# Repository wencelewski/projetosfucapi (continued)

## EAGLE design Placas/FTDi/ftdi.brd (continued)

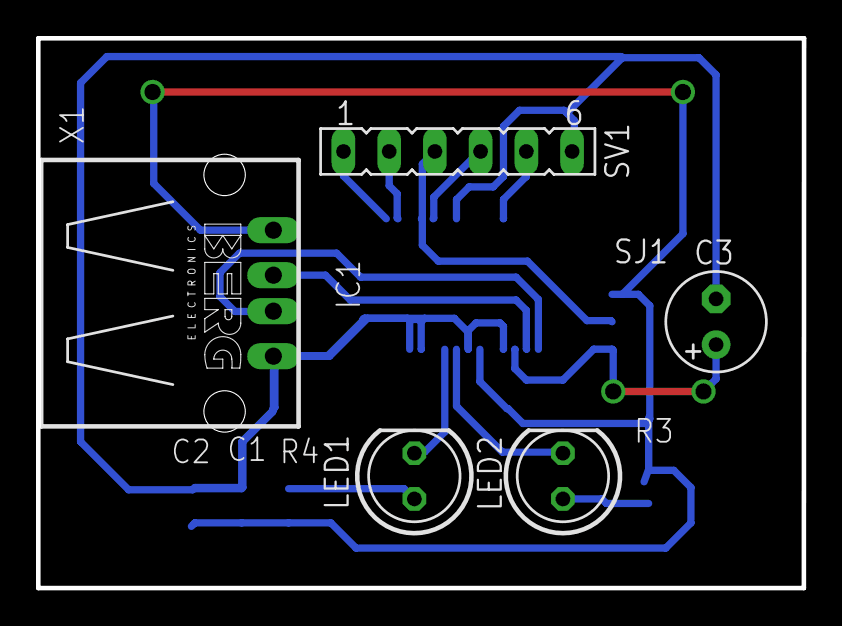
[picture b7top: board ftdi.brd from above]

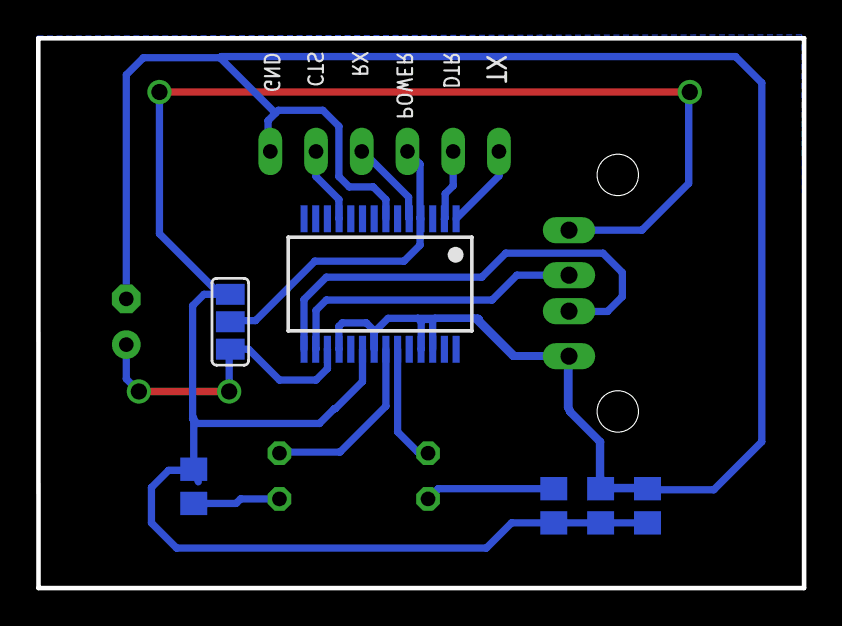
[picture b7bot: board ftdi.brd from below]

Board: 2 copper layers, 42.5 x 30.5 mm, 11 parts (6 on the bottom side), 14 nets.

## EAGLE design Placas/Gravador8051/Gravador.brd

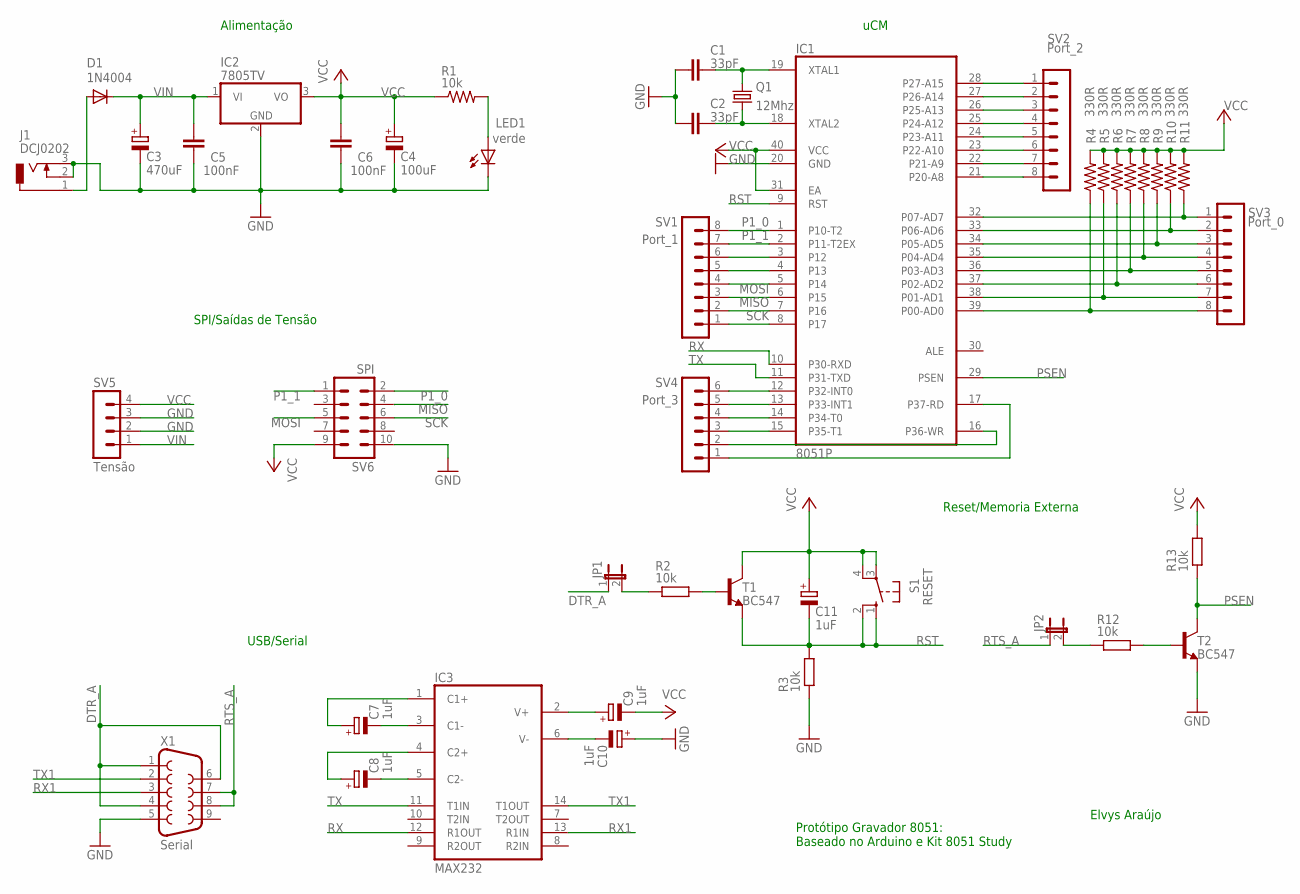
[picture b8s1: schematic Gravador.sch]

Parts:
C1, C2: 33pF; C5B3
C3: 470uF; E3,5-8
C4: 100uF; E2,5-6E
C5, C6: 100nF; C5B3
C7, C8, C9, C10, C11: 1uF; E2,5-6E
D1: 1N4004; DO41-10
IC1: 8051P; DIL40
IC2: 7805TV; TO220V
IC3: MAX232; DIL16
J1: DCJ0202
JP1, JP2: JP1E; JP1
LED1: verde; LED5MM
Q1: 12Mhz; HC49U-V
R1: 10k; 0207/2V
R2, R3, R12, R13: 10k; 0207/10@1
R4, R5, R6, R7, R8, R9, R10, R11: 330R; 0207/2V
S1: RESET; B3F-10XX
SV1: Port_1; MA08-1
SV2: Port_2; MA08-1
SV3: Port_0; MA08-1
SV4: Port_3; MA06-1
SV5: Tensão; MA04-1
SV6: SPI; MA05-2
T1, T2: BC547; TO92
X1: Serial; F09HP

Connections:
DTR_A: JP1.1, X1.1, X1.4, X1.6
GND: C1.2, C2.2, C3.-, C4.-, C5.2, C6.2, C10.+, IC1.20 (GND), IC2.2 (GND), IC3.15 (GND), J1.2, J1.3, LED1.K (C), R3.1, SV5.2, SV5.3, SV6.10, T2.1 (E), X1.5
MISO: IC1.7 (P16), SV1.2, SV6.4
MOSI: IC1.6 (P15), SV1.3, SV6.5
unnamed: C1.1, IC1.19 (XTAL1), Q1.1
unnamed: C2.1, IC1.18 (XTAL2), Q1.2
unnamed: IC1.15 (P35-T1), SV4.3
unnamed: IC1.14 (P34-T0), SV4.4
unnamed: IC1.5 (P14), SV1.4
unnamed: IC1.4 (P13), SV1.5
unnamed: IC1.3 (P12), SV1.6
unnamed: IC1.28 (P27-A15), SV2.1
unnamed: IC1.27 (P26-A14), SV2.2
unnamed: IC1.26 (P25-A13), SV2.3
unnamed: IC1.25 (P24-A12), SV2.4
unnamed: IC1.24 (P23-A11), SV2.5
unnamed: IC1.23 (P22-A10), SV2.6
unnamed: IC1.22 (P21-A9), SV2.7
unnamed: IC1.21 (P20-A8), SV2.8
unnamed: IC1.13 (P33-INT1), SV4.5
unnamed: IC1.32 (P07-AD7), R11.1, SV3.1
unnamed: IC1.33 (P06-AD6), R10.1, SV3.2
unnamed: IC1.34 (P05-AD5), R9.1, SV3.3
unnamed: IC1.35 (P04-AD4), R8.1, SV3.4
unnamed: IC1.36 (P03-AD3), R7.1, SV3.5
unnamed: IC1.37 (P02-AD2), R6.1, SV3.6
unnamed: IC1.38 (P01-AD1), R5.1, SV3.7
unnamed: IC1.12 (P32-INT0), SV4.6
unnamed: IC1.16 (P36-WR), SV4.2
unnamed: IC1.17 (P37-RD), SV4.1
unnamed: LED1.A, R1.2
unnamed: C7.+, IC3.1 (C1+)
unnamed: D1.A, J1.1
unnamed: C7.-, IC3.3 (C1-)
unnamed: C8.+, IC3.4 (C2+)
unnamed: C8.-, IC3.5 (C2-)
unnamed: C9.+, IC3.2 (V+)
unnamed: C10.-, IC3.6 (V-)
unnamed: JP1.2, R2.1
unnamed: R2.2, T1.2 (B)
unnamed: IC1.39 (P00-AD0), R4.1, SV3.8
unnamed: JP2.2, R12.1
unnamed: R12.2, T2.2 (B)
P1_0: IC1.1 (P10-T2), SV1.8, SV6.2
P1_1: IC1.2 (P11-T2EX), SV1.7, SV6.1
PSEN: IC1.29 (PSEN), R13.1, T2.3 (C)
RST: C11.-, IC1.9 (RST), R3.2, S1.1 (S), S1.2 (S1), T1.1 (E)
RTS_A: JP2.1, X1.7, X1.8
RX: IC1.10 (P30-RXD), IC3.12 (R1OUT)
RX1: IC3.13 (R1IN), X1.3
SCK: IC1.8 (P17), SV1.1, SV6.6
TX: IC1.11 (P31-TXD), IC3.11 (T1IN)
TX1: IC3.14 (T1OUT), X1.2
VCC: C4.+, C6.1, C9.-, C11.+, IC1.31 (EA), IC1.40 (VCC), IC2.3 (VO), IC3.16 (VCC), R1.1, R4.2, R5.2, R6.2, R7.2, R8.2, R9.2, R10.2, R11.2, R13.2, S1.3, S1.4 (P1), SV5.4, SV6.9, T1.3 (C)
VIN: C3.+, C5.1, D1.C, IC2.1 (VI), SV5.1

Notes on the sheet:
Alimentação
USB/Serial
SPI/Saídas de Tensão
Reset/Memoria Externa
uCM
Elvys Araújo
Protótipo Gravador 8051: Baseado no Arduino e Kit 8051 Study

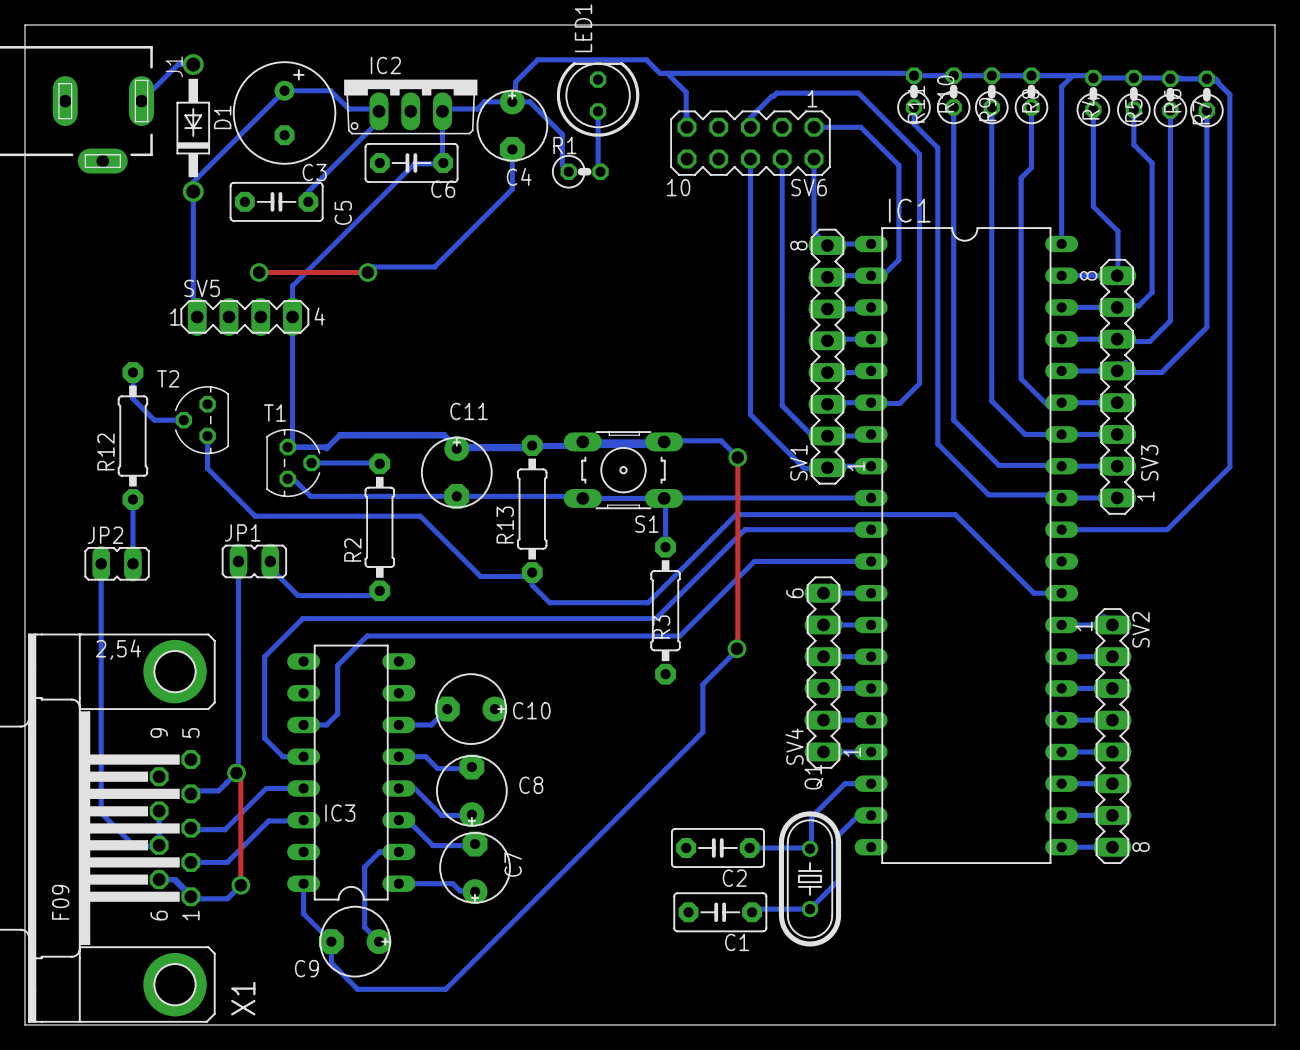
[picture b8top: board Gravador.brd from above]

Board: 2 copper layers, 100.0 x 80.0 mm, 43 parts (0 on the bottom side), 55 nets.

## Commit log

2014-08-11 Commit Inicial
